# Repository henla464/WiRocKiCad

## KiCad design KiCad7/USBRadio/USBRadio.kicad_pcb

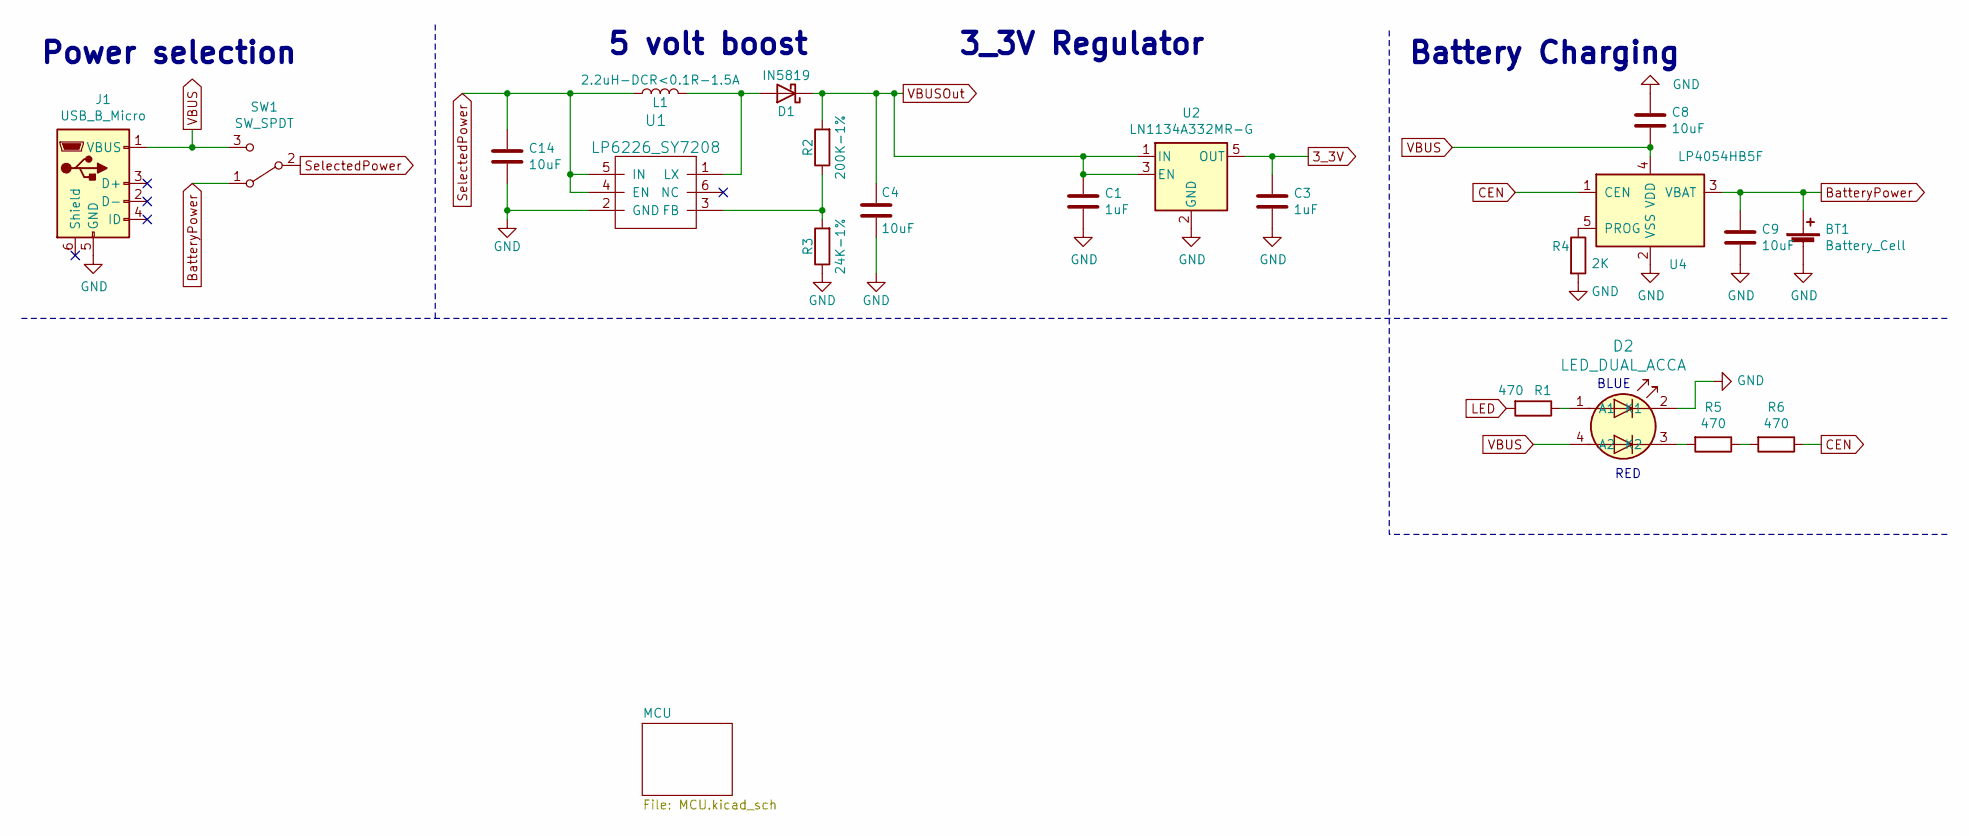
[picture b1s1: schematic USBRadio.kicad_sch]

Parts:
BT1: Battery_Cell; JST_2.56
C1, C3: 1uF; C_0603_1608Metric_Pad1.08x0.95mm_HandSolder; ManufacturerPartNumber CL10A105KB8NNNC; LCSC Part # C15849
C4, C8, C9, C14: 10uF; C_0603_1608Metric_Pad1.08x0.95mm_HandSolder; ManufacturerPartNumber CL10A106KP8NNNC; LCSC Part # C19702
D1: IN5819; D_SOD-123; ManufacturerPartNumber B5817W; LCSC Part # C8597
D2: LED_DUAL_ACCA; LED_Dual_1.7_1.6; ManufacturerPartNumber HL-PCB-1617S9FH203BC; LCSC Part # C513363
J1: USB_B_Micro; USB_Micro-B_Horizontal; ManufacturerPartNumber U254-051T-4BH83-F1S; LCSC Part # C397452
L1: 2.2uH-DCR<0.1R-1.5A; Inductor_SLW4018; ManufacturerPartNumber SLW4018S2R2MST; LCSC Part # C206341
R1, R5, R6: 470; R_0805_2012Metric_Pad1.20x1.40mm_HandSolder; ManufacturerPartNumber 0805W8F4700T5E; LCSC Part # C17710
R2: 200K-1%; C_0603_1608Metric_Pad1.08x0.95mm_HandSolder; ManufacturerPartNumber 0603WAF2003T5E; LCSC Part # C25811
R3: 24K-1%; C_0603_1608Metric_Pad1.08x0.95mm_HandSolder; ManufacturerPartNumber 0603WAF2402T5E; LCSC Part # C23352
R4: 2K; R_0805_2012Metric_Pad1.20x1.40mm_HandSolder; ManufacturerPartNumber 0805W8F2001T5E; LCSC Part # C17604
SW1: SW_SPDT; SW_SPDT_PCM12; ManufacturerPartNumber SK-3296S-01-L3; LCSC Part # C319019
U1: LP6226_SY7208; TSOT-23-6_HandSoldering; ManufacturerPartNumber SY7208ABC; LCSC Part # C80514
U2: LN1134A332MR-G; SOT-23-5; ManufacturerPartNumber LN1134A332MR-G; LCSC Part # C141419
U4: LP4054HB5F; SOT-23-5; ManufacturerPartNumber LP4054HB5F; LCSC Part # C517187

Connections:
3_3V: C3.1, U2.5 (OUT); also elsewhere on the board
BatteryPower: BT1.1 (+), C9.1, SW1.1 (A), U4.3 (VBAT)
CEN: R6.1, U4.1 (CEN)
GND: BT1.2 (-), C1.2, C3.2, C4.2, C8.1, C9.2, C14.2, D2.2 (K1), J1.5 (GND), R3.1, R4.2, U1.2 (GND), U2.2 (GND), U4.2 (VSS); also elsewhere on the board
LED: R1.2; also elsewhere on the board
unnamed: D1.2 (A), L1.2, U1.1 (LX)
unnamed: D2.1 (A1), R1.1
unnamed: D2.3 (K2), R5.2
unnamed: R5.1, R6.2
unnamed: R2.1, R3.2, U1.3 (FB)
unnamed: R4.1, U4.5 (PROG)
SelectedPower: C14.1, L1.1, SW1.2 (B), U1.4 (EN), U1.5 (IN)
VBUS: C8.2, D2.4 (A2), J1.1 (VBUS), SW1.3 (C), U4.4 (VDD)
VBUSOut: C1.1, C4.1, D1.1 (K), R2.2, U2.1 (IN), U2.3 (EN); also elsewhere on the board

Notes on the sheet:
RED
Power selection
BLUE
5 volt boost
3_3V Regulator
Battery Charging

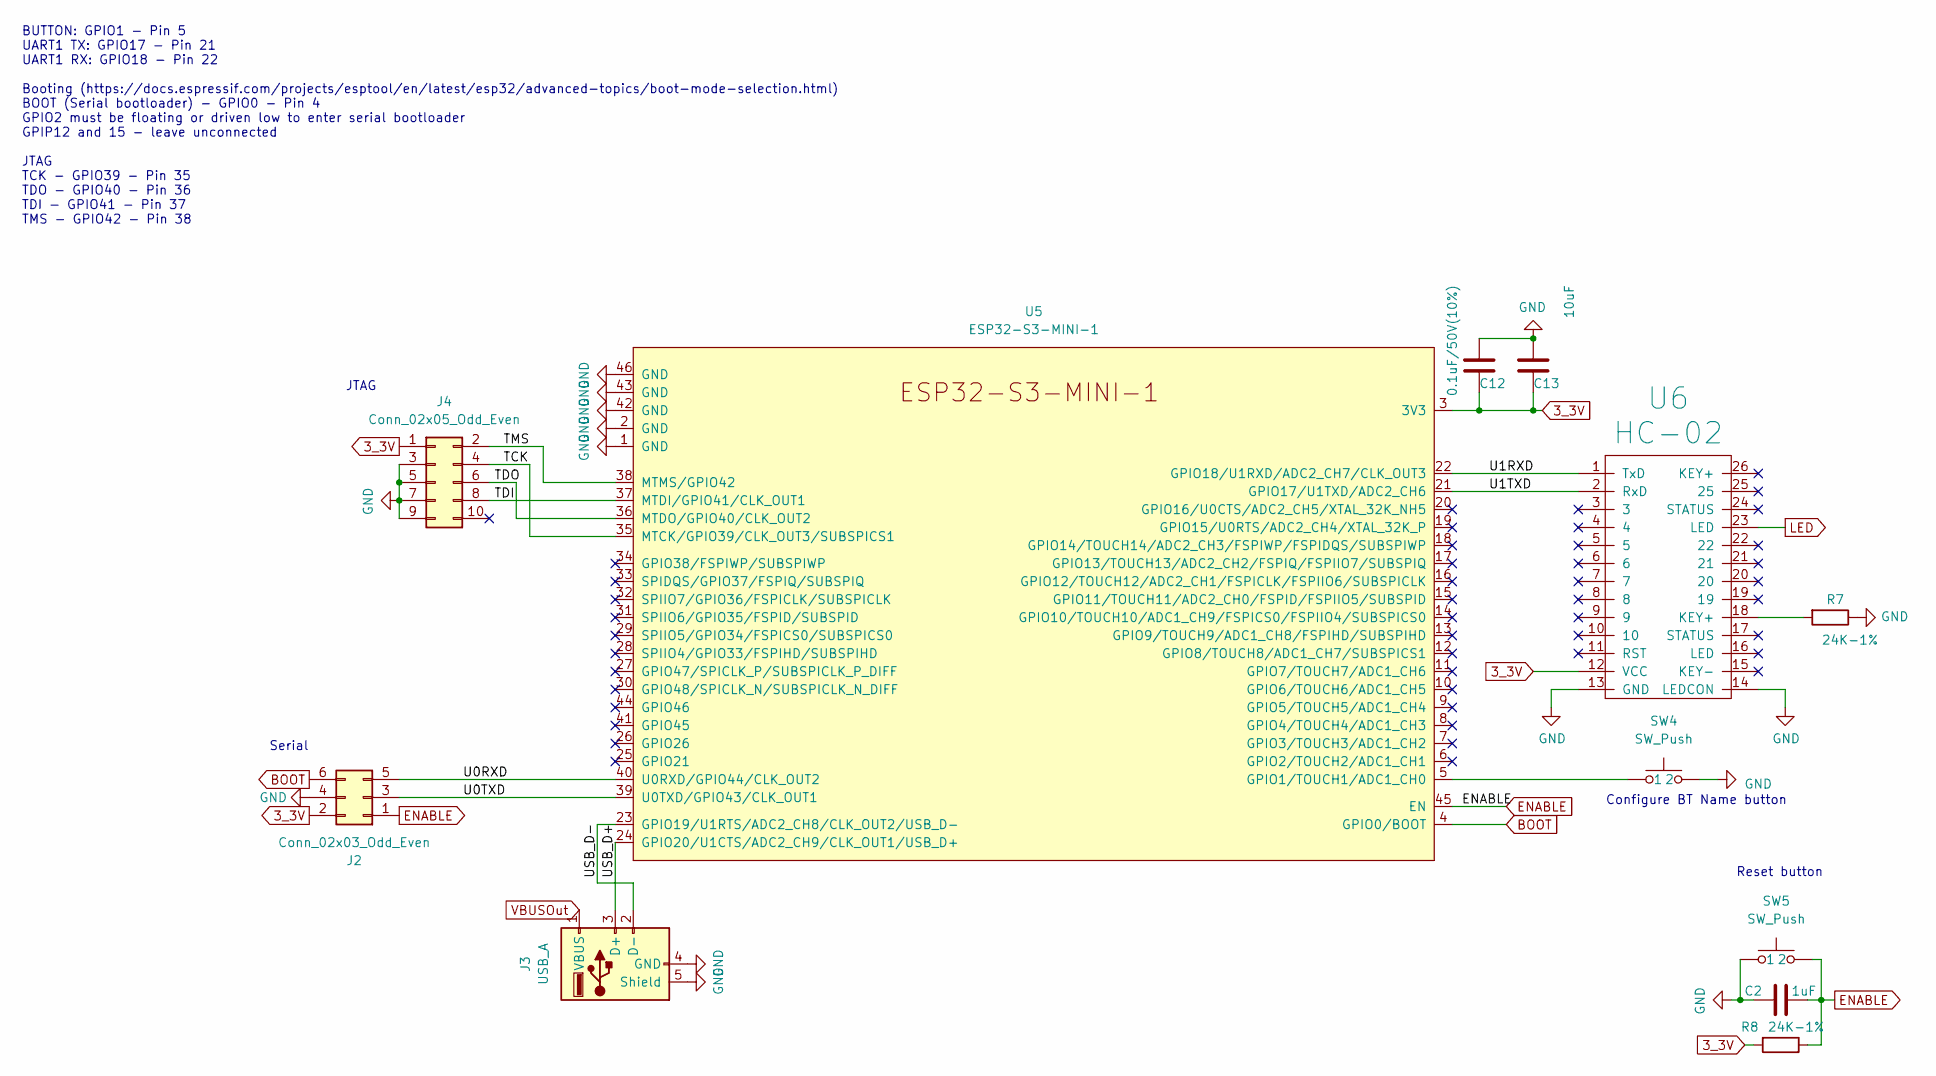
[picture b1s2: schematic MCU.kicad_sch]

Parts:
C2: 1uF; C_0603_1608Metric_Pad1.08x0.95mm_HandSolder; ManufacturerPartNumber CL10A105KB8NNNC; LCSC Part # C15849
C12: 0.1uF/50V(10%); C_0805_2012Metric_Pad1.18x1.45mm_HandSolder; ManufacturerPartNumber CC0805KRX7R9BB104; LCSC Part # C49678
C13: 10uF; C_0603_1608Metric_Pad1.08x0.95mm_HandSolder; ManufacturerPartNumber CL10A106KP8NNNC; LCSC Part # C19702
J2: Conn_02x03_Odd_Even; IDC-Header_2x03_P1.27mm_Vertical_SMD
J3: USB_A; USB_A_CONNFLY_DS1095-WNR0
J4: Conn_02x05_Odd_Even; IDC-Header_2x05_P1.27mm_Vertical_SMD
R7, R8: 24K-1%; C_0603_1608Metric_Pad1.08x0.95mm_HandSolder; ManufacturerPartNumber 0603WAF2402T5E; LCSC Part # C23352
SW4, SW5: SW_Push; SW_SPST_TL3342; ManufacturerPartNumber TS-1187A-B-A-B; LCSC Part # C318884
U5: ESP32-S3-MINI-1
U6: HC-02

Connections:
3_3V: C12.1, C13.1, J2.2, J4.1, R8.2, U5.3 (3V3), U6.12 (VCC); also elsewhere on the board
/MCU/TCK: J4.4, U5.35 (MTCK/GPIO39/CLK_OUT3/SUBSPICS1)
/MCU/TDI: J4.8, U5.37 (MTDI/GPIO41/CLK_OUT1)
/MCU/TDO: J4.6, U5.36 (MTDO/GPIO40/CLK_OUT2)
/MCU/TMS: J4.2, U5.38 (MTMS/GPIO42)
/MCU/U0RXD: J2.5, U5.40 (U0RXD/GPIO44/CLK_OUT2)
/MCU/U0TXD: J2.3, U5.39 (U0TXD/GPIO43/CLK_OUT1)
/MCU/U1RXD: U5.22 (GPIO18/U1RXD/ADC2_CH7/CLK_OUT3), U6.1 (TxD)
/MCU/U1TXD: U5.21 (GPIO17/U1TXD/ADC2_CH6), U6.2 (RxD)
/MCU/USB_D+: J3.3 (D+), U5.24 (GPIO20/U1CTS/ADC2_CH9/CLK_OUT1/USB_D+)
/MCU/USB_D-: J3.2 (D-), U5.23 (GPIO19/U1RTS/ADC2_CH8/CLK_OUT2/USB_D-)
BOOT: J2.6, U5.4 (GPIO0/BOOT)
ENABLE: C2.2, J2.1, R8.1, SW5.2, U5.45 (EN)
GND: C2.1, C12.2, C13.2, J2.4, J3.4 (GND), J3.5 (Shield), J4.3, J4.5, J4.7, J4.9, R7.1, SW4.2, SW5.1, U5.1 (GND), U5.2 (GND), U5.42 (GND), U5.43 (GND), U5.46 (GND), U6.13 (GND), U6.14 (LEDCON); also elsewhere on the board
LED: U6.23 (LED); also elsewhere on the board
unnamed: R7.2, U6.18 (KEY+)
unnamed: SW4.1, U5.5 (GPIO1/TOUCH1/ADC1_CH0)
VBUSOut: J3.1 (VBUS); also elsewhere on the board

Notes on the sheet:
Reset button
JTAG
BUTTON: GPIO1 - Pin 5 UART1 TX: GPIO17 - Pin 21 UART1 RX: GPIO18 - Pin 22 Booting (https://docs.espressif.com/projects/esptool/en/latest/esp32/advanced-topics/boot-mode-selection.html) BOOT (Serial bootloader) - GPIO0 - Pin 4 GPIO2 must be floating or driven low to enter serial bootloader GPIP12 an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
Serial
Configure BT Name button

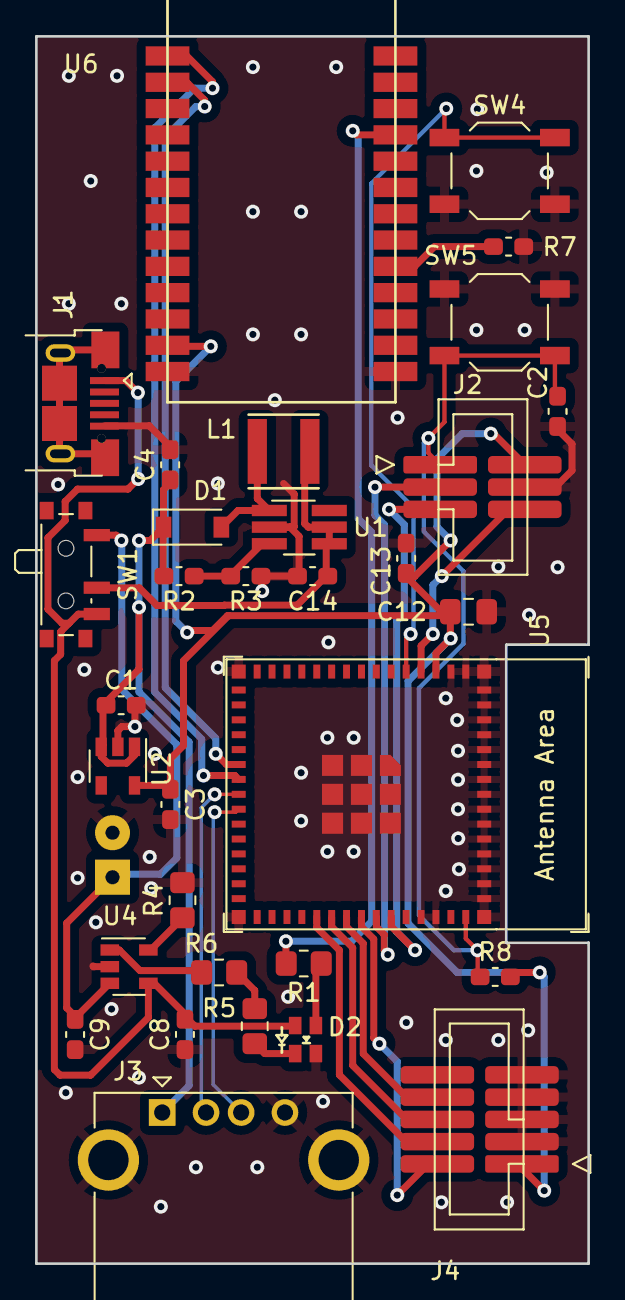
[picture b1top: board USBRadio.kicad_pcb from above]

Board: 2 copper layers, 31.5 x 70.0 mm, 33 parts (1 on the bottom side), 28 nets.

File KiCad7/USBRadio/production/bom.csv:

Designator,Footprint,Quantity,Value,LCSC Part #
BT1,JST_2.56,1,Battery_Cell,
"C1, C2, C3",C_0603_1608Metric_Pad1.08x0.95mm_HandSolder,3,1uF,
C12,C_0805_2012Metric_Pad1.18x1.45mm_HandSolder,1,0.1uF/50V(10%),
"C13, C14, C4, C8, C9",C_0603_1608Metric_Pad1.08x0.95mm_HandSolder,5,10uF,
D1,D_SOD-123,1,IN5819,
D2,LED_Dual_1.7_1.6,1,LED_DUAL_ACCA,
J1,USB_Micro-B_Horizontal,1,USB_B_Micro,
J2,IDC-Header_2x03_P1.27mm_Vertical_SMD,1,Conn_02x03_Odd_Even,
J3,USB_A_CONNFLY_DS1095-WNR0,1,USB_A,
J4,IDC-Header_2x05_P1.27mm_Vertical_SMD,1,Conn_02x05_Odd_Even,
L1,Inductor_SLW4018,1,2.2uH-DCR<0.1R-1.5A,
"R1, R5, R6",R_0805_2012Metric_Pad1.20x1.40mm_HandSolder,3,470,
R2,C_0603_1608Metric_Pad1.08x0.95mm_HandSolder,1,200K-1%,
"R3, R7, R8",C_0603_1608Metric_Pad1.08x0.95mm_HandSolder,3,24K-1%,
R4,R_0805_2012Metric_Pad1.20x1.40mm_HandSolder,1,2K,
SW1,SW_SPDT_PCM12,1,SW_SPDT,
"SW4, SW5",SW_SPST_TL3342,2,SW_Push,
U1,TSOT-23-6_HandSoldering,1,LP6226_SY7208,
U2,SOT-23-5,1,LN1134A332MR-G,
U4,SOT-23-5,1,LP4054HB5F,
U5,ESP32-S3-MINI-1,1,ESP32-S3-MINI-1,
U6,HC-02,1,HC-02,

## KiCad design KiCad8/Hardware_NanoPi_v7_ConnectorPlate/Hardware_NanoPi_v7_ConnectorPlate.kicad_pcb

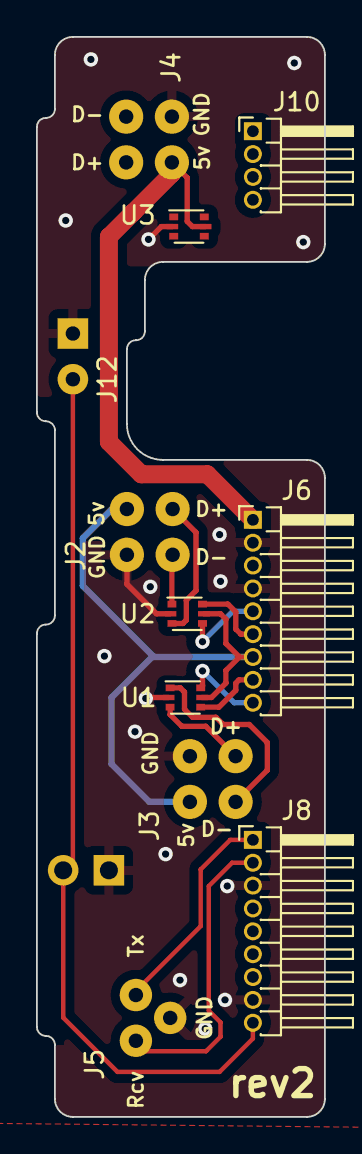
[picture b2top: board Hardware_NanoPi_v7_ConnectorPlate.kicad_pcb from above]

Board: 2 copper layers, 16.0 x 60.0 mm, 12 parts (1 on the bottom side), 14 nets.

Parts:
J2: USB_Host_Data_02x02; USBConnPads7
J3: USB_Host_Data_02x02; USBConnPads8
J4: USB_Power_02x02; USBConnPads7
J5: Conn_01x03; SerialConnPads3Pin
J6, J8: Conn_01x09; PinHeader_1x09_P1.27mm_Horizontal
J10: Conn_01x04; PinHeader_1x04_P1.27mm_Horizontal
J11: Conn_01x02; PinHeader_1x02_P2.54mm_Horizontal
J12: Conn_01x02; PwrBtnPads
U1, U2, U3: USBLC6-2P6; SOT-666

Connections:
GND: J2.4, J3.4, J4.4, J5.3, J6.2, J6.4, J8.3, J8.8, J11.1, J12.1, U1.2 (GND), U2.2 (GND), U3.2 (GND)
unnamed: J2.2, U2.1 (I/O1)
unnamed: J2.3, U2.3 (I/O2)
unnamed: J3.2, U1.1 (I/O1)
unnamed: J3.3, U1.3 (I/O2)
PWRBTN: J8.9, J11.2, J12.2
R2IN: J5.1, J8.2
T2OUT: J5.2, J8.1
USBHost-DM1: J6.6, U2.6 (I/O1)
USBHost-DM2: J6.9, U1.6 (I/O1)
USBHost-DP1: J6.5, U2.4 (I/O2)
USBHost-DP2: J6.8, U1.4 (I/O2)
VBUS: J4.1, J6.1, U3.5 (VBUS)
VDD_5V: J2.1, J3.1, J6.7, U1.5 (VBUS), U2.5 (VBUS)

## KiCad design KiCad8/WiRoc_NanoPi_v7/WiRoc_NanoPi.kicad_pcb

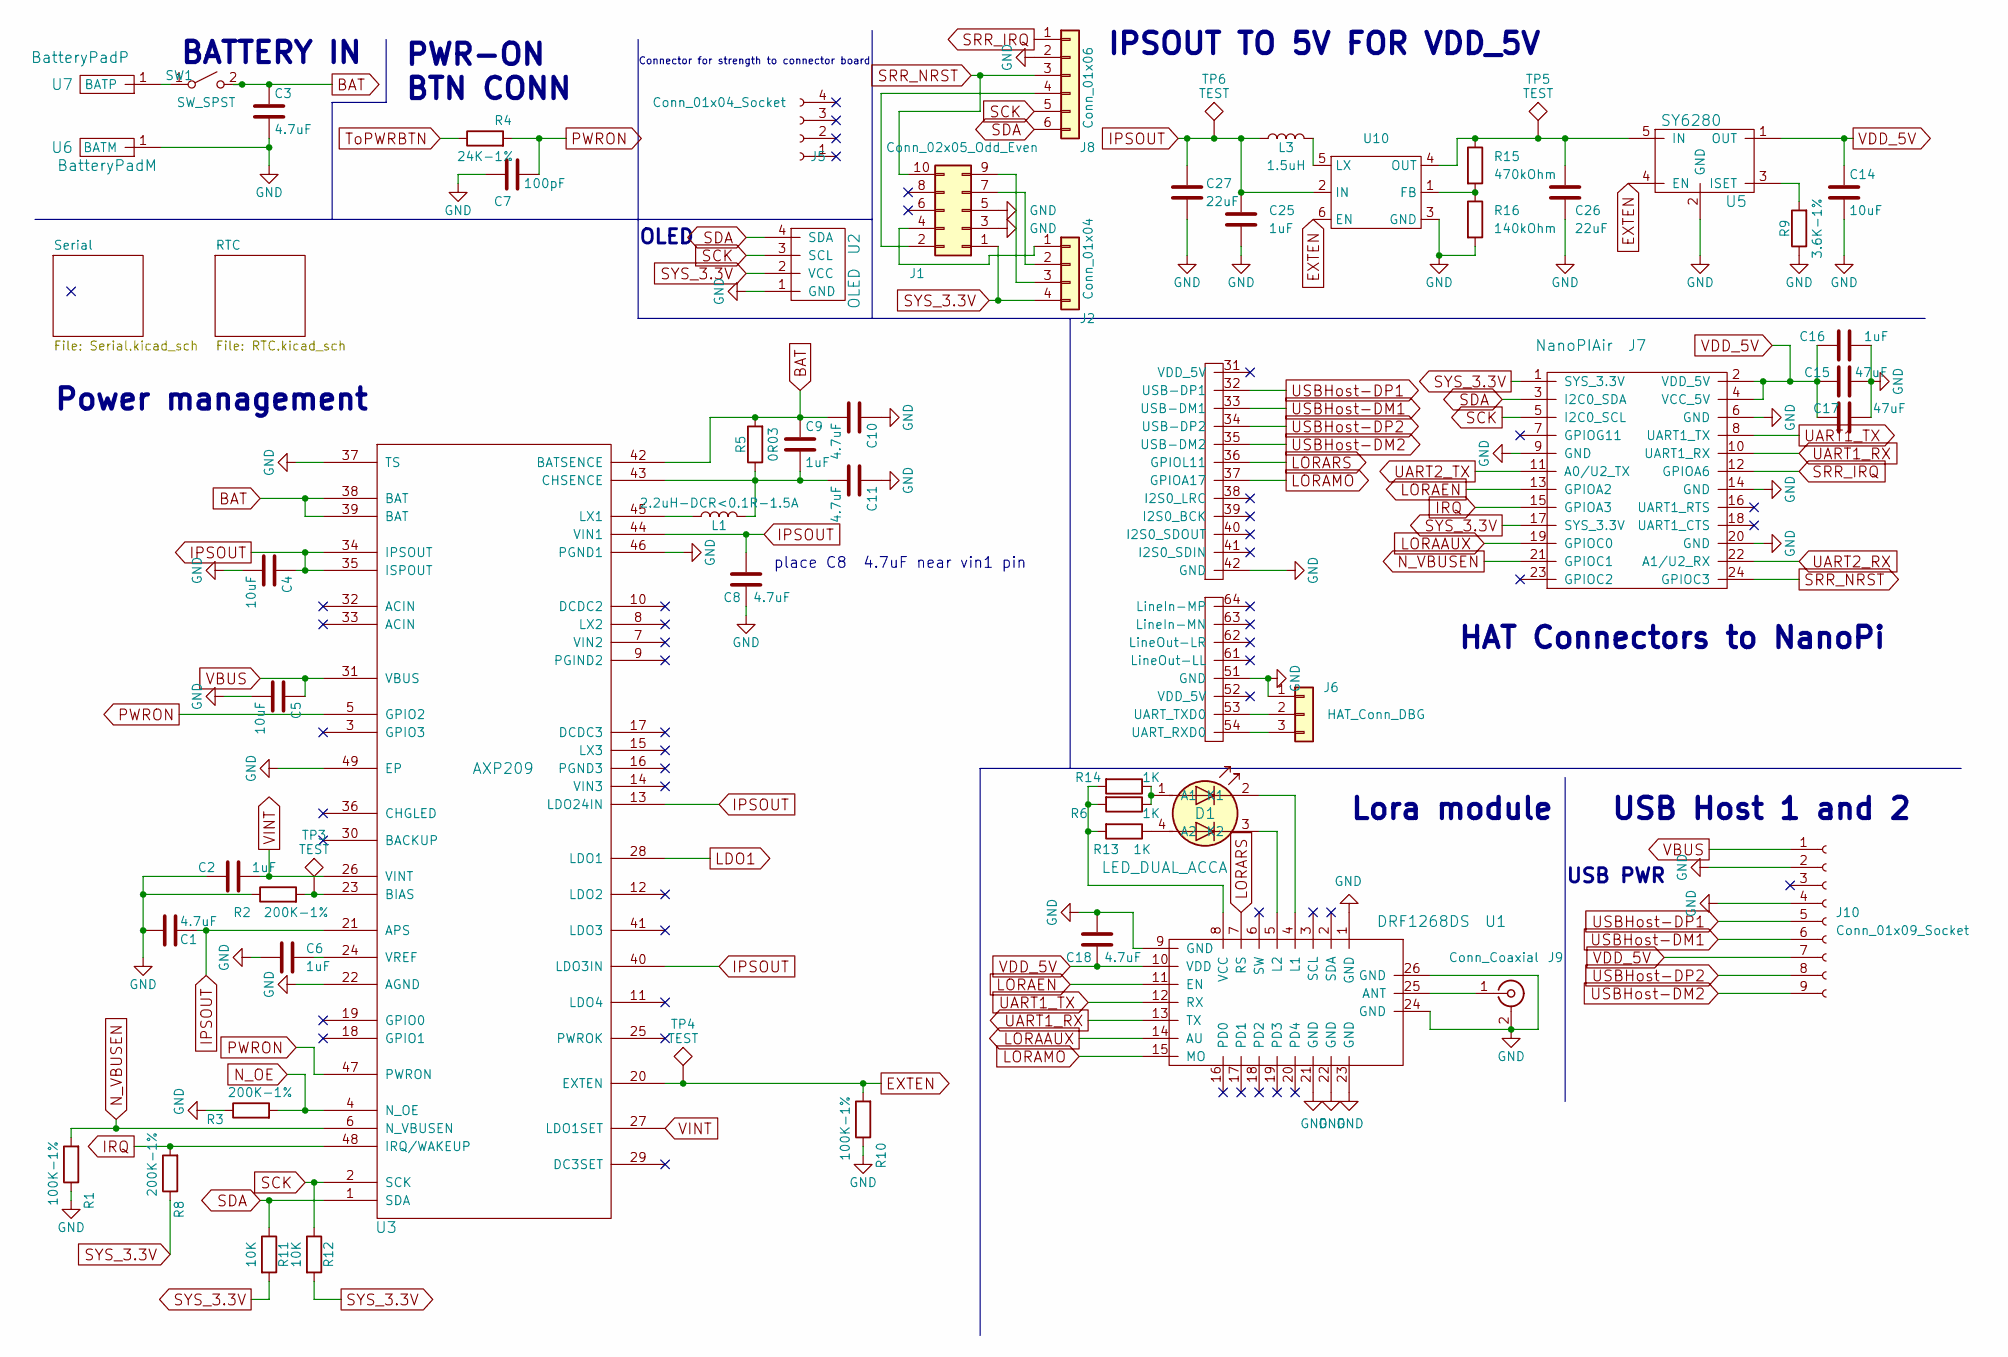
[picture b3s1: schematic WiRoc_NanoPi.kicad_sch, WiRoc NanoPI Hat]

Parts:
C1, C3, C8, C10, C11, C18: 4.7uF; C_0603_1608Metric; ManufacturerPartNumber CL10A475KO8NNNC; LCSC Part # C19666
C2, C6, C9, C16, C25: 1uF; C_0603_1608Metric; ManufacturerPartNumber CL10A105KB8NNNC; LCSC Part # C15849
C4, C5, C14: 10uF; C_0603_1608Metric; ManufacturerPartNumber CL10A106KP8NNNC; LCSC Part # C19702
C7: 100pF; C_0603_1608Metric; ManufacturerPartNumber CL10C101JB8NNNC; LCSC Part # C14858
C15, C17: 47uF; C_1206_3216Metric; ManufacturerPartNumber CL31A476MPHNNNE; LCSC Part # C96123
C26, C27: 22uF; C_0603_1608Metric; PartNo GRM188R61A226ME15D; LCSC Part # C84419
D1: LED_DUAL_ACCA; LED_Dual_1.7_1.6; ManufacturerPartNumber HL-PCB-1617S9FH203BC; LCSC Part # C513363
J1: Conn_02x05_Odd_Even; PinHeader_2x05_P1.27mm_Vertical
J2: Conn_01x04; PinHeader_1x04_P1.27mm_Horizontal
J5: Conn_01x04_Socket; PinSocket_1x04_P1.27mm_Vertical
J6: HAT_Conn_DBG; Pin_Header_Straight_1x03_Pitch2.54mm; ManufacturerPartNumber 2.54mm 1x40P
J7: NanoPIAir; NanoPiNeoAirAllPins; ManufacturerPartNumber 2.54mm 2x40P
J8: Conn_01x06; PinHeader_1x06_P1.27mm_Horizontal
J9: Conn_Coaxial; SMA_Amphenol_901-143_Horizontal
J10: Conn_01x09_Socket; PinSocket_1x09_P1.27mm_Vertical
L1: 2.2uH-DCR<0.1R-1.5A; Inductor_SLW4018; ManufacturerPartNumber SLW4018S2R2MST; LCSC Part # C206341
L3: 1.5uH; Inductor_SLW4018; PartNo SLW4020S1R5MST; LCSC Part # C206395
R1, R10: 100K-1%; R_0603_1608Metric; ManufacturerPartNumber 0603WAF1003T5E; LCSC Part # C25803
R2, R3, R8: 200K-1%; R_0603_1608Metric; ManufacturerPartNumber 0603WAF2003T5E; LCSC Part # C25811
R4: 24K-1%; R_0603_1608Metric; ManufacturerPartNumber 0603WAF2402T5E; LCSC Part # C23352
R5: 0R03; R_0805_2012Metric; ManufacturerPartNumber 0805W4F300MT5E; LCSC Part # C247605
R6, R13, R14: 1K; R_0603_1608Metric; ManufacturerPartNumber 0603WAJ0102T5E; LCSC Part # C21190
R9: 3.6K-1%; R_0603_1608Metric; ManufacturerPartNumber 0603WAF3601T5E; LCSC Part # C22980
R11, R12: 10K; R_0603_1608Metric; ManufacturerPartNumber 0603WAF1002T5E; LCSC Part # C25804
R15: 470kOhm; R_0603_1608Metric; PartNo HPCR0603F470KK9; LCSC Part # C23178
R16: 140kOhm; R_0603_1608Metric; PartNo 0603WAF140KT5E; LCSC Part # C321721
SW1: SW_SPST; Pin_Header_Straight_1x02_Pitch2.54mm; ManufacturerPartNumber 2.54mm 1x40P
TP3, TP4, TP5, TP6: TEST; TestPoint_Pad_D1.0mm
U1: DRF1268DS
U2: OLED; CONN_OLED_TWI-Socket_Strip_Straight_1x04_Pitch2.54mm; ManufacturerPartNumber 2.54mm 1x40P
U3: AXP209; qfn48_6x6mm_Pitch0.4mm; ManufacturerPartNumber AXP209; LCSC Part # C2997895
U5: SY6280; SOT-23-5; ManufacturerPartNumber SY6280AAC; LCSC Part # C55136
U6: BatteryPadM; BatteryPad
U7: BatteryPadP; BatteryPad
U10: TSOT-23-6; PartNo SY7069ADC; LCSC Part # C207630

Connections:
BAT: C3.1, C9.1, C10.2, R5.2, SW1.2 (B), U3.38 (BAT), U3.39 (BAT), U3.42 (BATSENCE)
EXTEN: R10.2, TP4.1, U3.20 (EXTEN), U5.4 (EN), U10.6 (EN)
GND: C1.2, C2.2, C3.2, C4.2, C5.2, C6.2, C7.1, C8.1, C10.1, C11.1, C14.2, C15.1, C16.2, C17.1, C18.2, C25.2, C26.2, C27.2, J1.3, J1.5, J6.1, J7.6 (GND), J7.9 (GND), J7.14 (GND), J7.20 (GND), J7.42 (GND), J7.51 (GND), J8.2, J9.2 (Ext), J10.2, J10.4, R1.1, R2.1, R3.1, R9.1, R10.1, R16.2, U1.1 (GND), U1.9 (GND), U1.21 (GND), U1.22 (GND), U1.23 (GND), U1.24 (GND), U1.26 (GND), U2.1 (GND), U3.22 (AGND), U3.37 (TS), U3.46 (PGND1), U3.49 (EP), U5.2 (GND), U6.1 (BATM), U10.3 (GND); also elsewhere on the board
IPSOUT: C1.1, C4.1, C8.2, C25.1, C27.1, L3.1, TP6.1, U3.13 (LDO24IN), U3.21 (APS), U3.34 (IPSOUT), U3.35 (ISPOUT), U3.40 (LDO3IN), U3.44 (VIN1), U10.2 (IN)
IRQ: J7.15 (GPIOA3), R8.2, U3.48 (IRQ/WAKEUP)
LDO1: U3.28 (LDO1); also elsewhere on the board
LORAAUX: J7.19 (GPIOC0), U1.14 (AU)
LORAEN: J7.13 (GPIOA2), U1.11 (EN)
LORAMO: J7.37 (GPIOA17), U1.15 (MO)
LORARS: J7.36 (GPIOL11), U1.7 (RS)
N_OE: R3.2, U3.4 (N_OE); also elsewhere on the board
N_VBUSEN: J7.21 (GPIOC1), R1.2, U3.6 (N_VBUSEN)
unnamed: D1.1 (A1), R6.1, R14.1
unnamed: D1.4 (A2), R13.1
unnamed: D1.2 (K1), U1.4 (L1)
unnamed: D1.3 (K2), U1.5 (L2)
unnamed: J1.2, J8.4
unnamed: J1.4, J2.1
unnamed: J1.7, J2.2
unnamed: J1.9, J2.3
unnamed: J6.2, J7.53 (UART_TXD0)
unnamed: J6.3, J7.54 (UART_RXD0)
unnamed: J9.1 (In), U1.25 (ANT)
unnamed: SW1.1 (A), U7.1 (BATP)
unnamed: R6.2, R13.2, R14.2, U1.8 (VCC)
unnamed: R2.2, TP3.1, U3.23 (BIAS)
unnamed: C9.2, C11.2, L1.2, R5.1, U3.43 (CHSENCE)
unnamed: L1.1, U3.45 (LX1)
unnamed: C6.1, U3.24 (VREF)
unnamed: R9.2, U5.3 (ISET)
unnamed: R15.2, R16.1, U10.1 (FB)
unnamed: L3.2, U10.5 (LX)
unnamed: C26.1, R15.1, TP5.1, U5.5 (IN), U10.4 (OUT)
PWRON: C7.2, R4.2, U3.5 (GPIO2), U3.47 (PWRON)
SCK: J7.5 (I2C0_SCL), J8.5, R12.1, U2.3 (SCL), U3.2 (SCK); also elsewhere on the board
SDA: J7.3 (I2C0_SDA), J8.6, R11.1, U2.4 (SDA), U3.1 (SDA); also elsewhere on the board
SRR_IRQ: J7.12 (GPIOA6), J8.1
SRR_NRST: J1.10, J7.24 (GPIOC3), J8.3
SYS_3.3V: J1.1, J2.4, J7.1 (SYS_3.3V), J7.17 (SYS_3.3V), R8.1, R11.2, R12.2, U2.2 (VCC); also elsewhere on the board
ToPWRBTN: R4.1; also elsewhere on the board
UART1_RX: J7.10 (UART1_RX), U1.13 (TX)
UART1_TX: J7.8 (UART1_TX), U1.12 (RX)
UART2_RX: J7.22 (A1/U2_RX); also elsewhere on the board
UART2_TX: J7.11 (A0/U2_TX); also elsewhere on the board
USBHost-DM1: J7.33 (USB-DM1), J10.6
USBHost-DM2: J7.35 (USB-DM2), J10.9
USBHost-DP1: J7.32 (USB-DP1), J10.5
USBHost-DP2: J7.34 (USB-DP2), J10.8
VBUS: C5.1, J10.1, U3.31 (VBUS)
VDD_5V: C14.1, C15.2, C16.1, C17.2, C18.1, J7.2 (VDD_5V), J7.4 (VCC_5V), J10.7, U1.10 (VDD), U5.1 (OUT)
VINT: C2.1, U3.26 (VINT), U3.27 (LDO1SET)

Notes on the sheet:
place C8 4.7uF near vin1 pin
USB PWR
Lora module
HAT Connectors to NanoPi
IPSOUT TO 5V FOR VDD_5V
PWR-ON BTN CONN
Power management
OLED
Connector for strength to connector board
USB Host 1 and 2
BATTERY IN

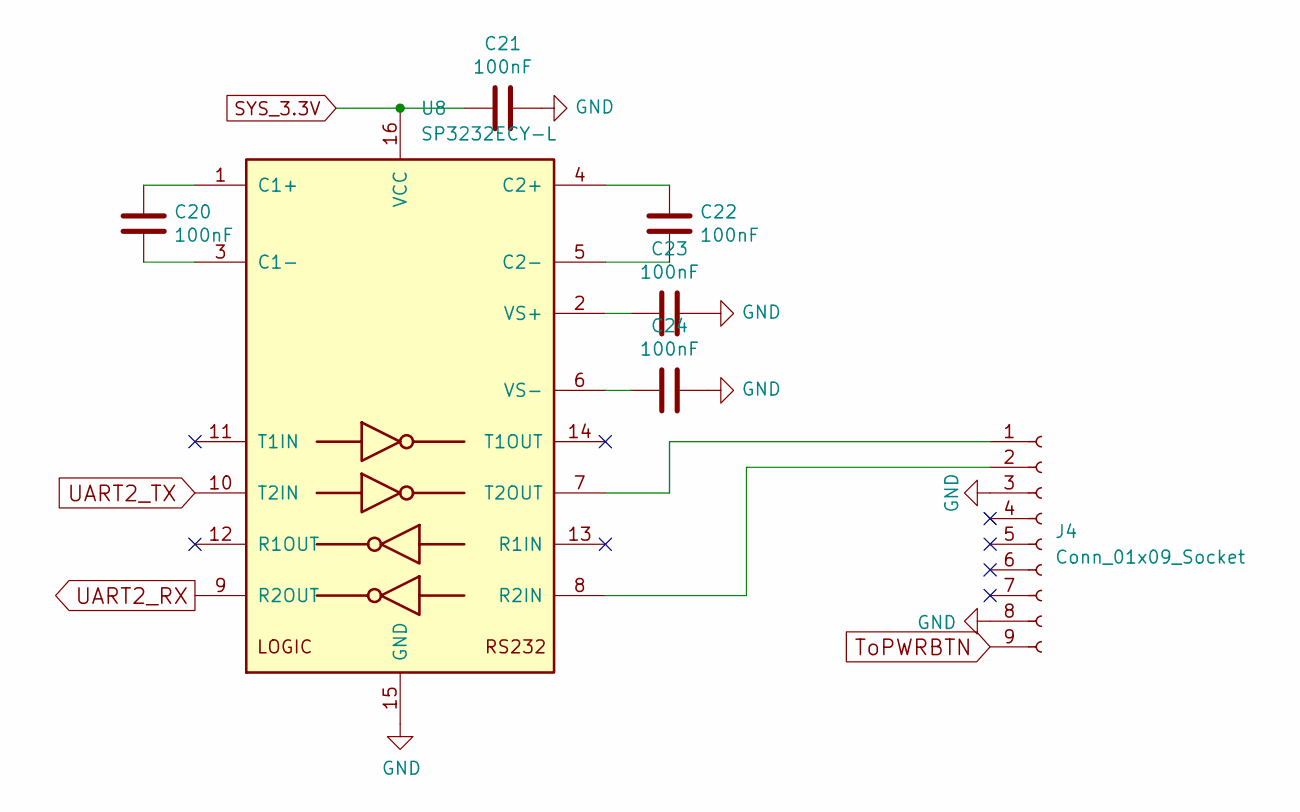
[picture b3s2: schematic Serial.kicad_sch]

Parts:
C20, C21, C22, C23, C24: 100nF; C_0603_1608Metric; ManufacturerPartNumber CC0603KRX7R9BB104; LCSC Part # C14663
J4: Conn_01x09_Socket; PinSocket_1x09_P1.27mm_Vertical
U8: SP3232ECY-L; TSSOP-16_4.4x5mm_P0.65mm; ManufacturerPartNumber SP3232ECY-L; LCSC Part # C3028967

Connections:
GND: C21.1, C23.1, C24.1, J4.3, J4.8, U8.15 (GND); also elsewhere on the board
unnamed: J4.1, U8.7 (T2OUT)
unnamed: J4.2, U8.8 (R2IN)
unnamed: C20.1, U8.1 (C1+)
unnamed: C20.2, U8.3 (C1-)
unnamed: C22.1, U8.4 (C2+)
unnamed: C22.2, U8.5 (C2-)
unnamed: C23.2, U8.2 (VS+)
unnamed: C24.2, U8.6 (VS-)
SYS_3.3V: C21.2, U8.16 (VCC); also elsewhere on the board
ToPWRBTN: J4.9; also elsewhere on the board
UART2_RX: U8.9 (R2OUT); also elsewhere on the board
UART2_TX: U8.10 (T2IN); also elsewhere on the board

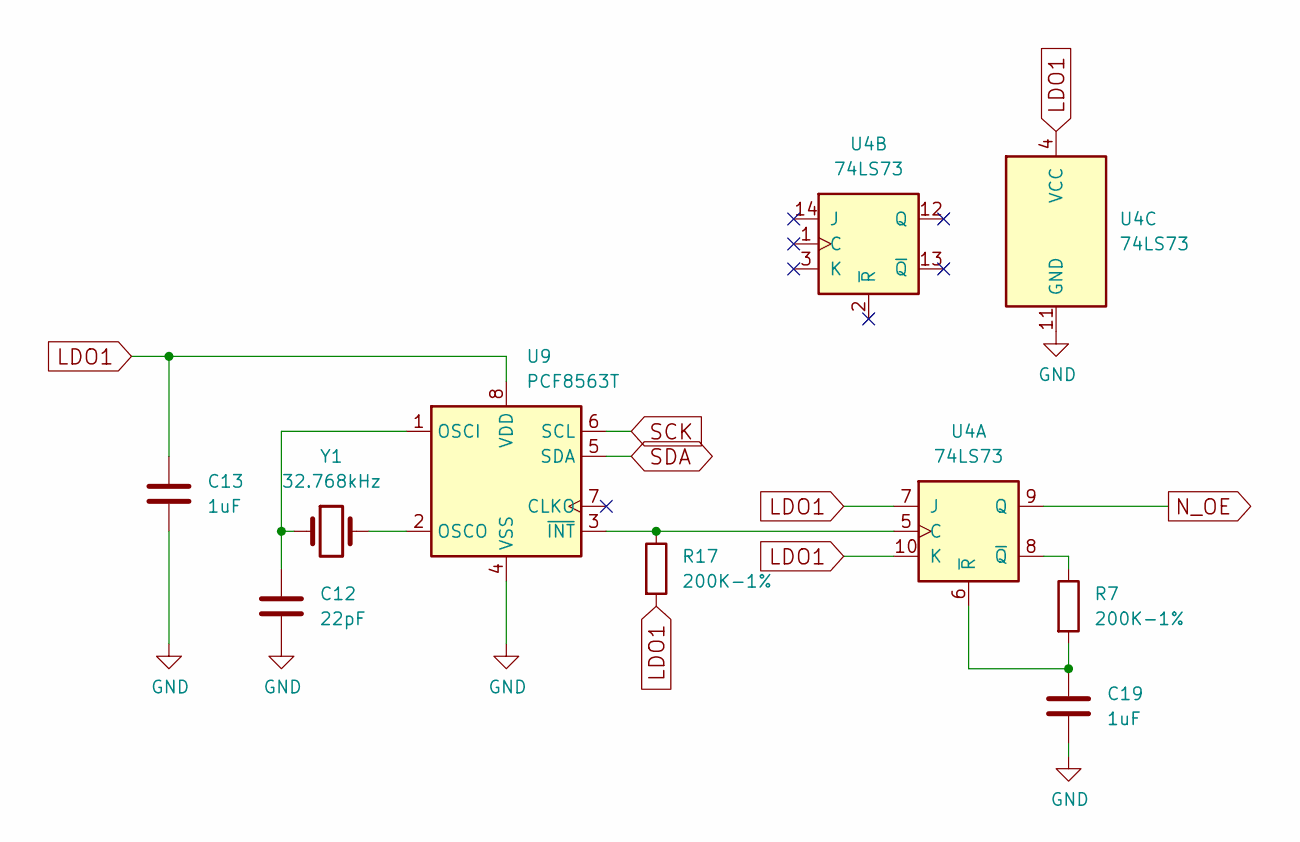
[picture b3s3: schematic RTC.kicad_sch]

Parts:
C12: 22pF; C_0402_1005Metric; ManufacturerPartNumber GRM155R71C223JA01D; LCSC Part # C1555
C13, C19: 1uF; C_0603_1608Metric; ManufacturerPartNumber CL10A105KB8NNNC; LCSC Part # C15849
R7, R17: 200K-1%; R_0603_1608Metric; ManufacturerPartNumber 0603WAF2003T5E; LCSC Part # C25811
U4: 74LS73; SOIC-14_3.9x8.7mm_P1.27mm; ManufacturerPartNumber CD74HC73M96; LCSC Part # C350539
U9: PCF8563T; SOIC-8_3.9x4.9mm_P1.27mm; ManufacturerPartNumber PCF8563T/5,518; LCSC Part # C7440
Y1: 32.768kHz; SMD3215-2P; ManufacturerPartNumber Q13FC1350000400; LCSC Part # C32346

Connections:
GND: C12.2, C13.2, C19.2, U4.11 (GND), U9.4 (VSS); also elsewhere on the board
LDO1: C13.1, R17.2, U4.4 (VCC), U4.7 (J), U4.10 (K), U9.8 (VDD); also elsewhere on the board
N_OE: U4.9 (Q); also elsewhere on the board
unnamed: R17.1, U4.5 (C), U9.3 (~INT)
unnamed: R7.1, U4.8 (~Q)
unnamed: C19.1, R7.2, U4.6 (~R)
unnamed: C12.1, U9.1 (OSCI), Y1.1
unnamed: U9.2 (OSCO), Y1.2
SCK: U9.6 (SCL); also elsewhere on the board
SDA: U9.5 (SDA); also elsewhere on the board

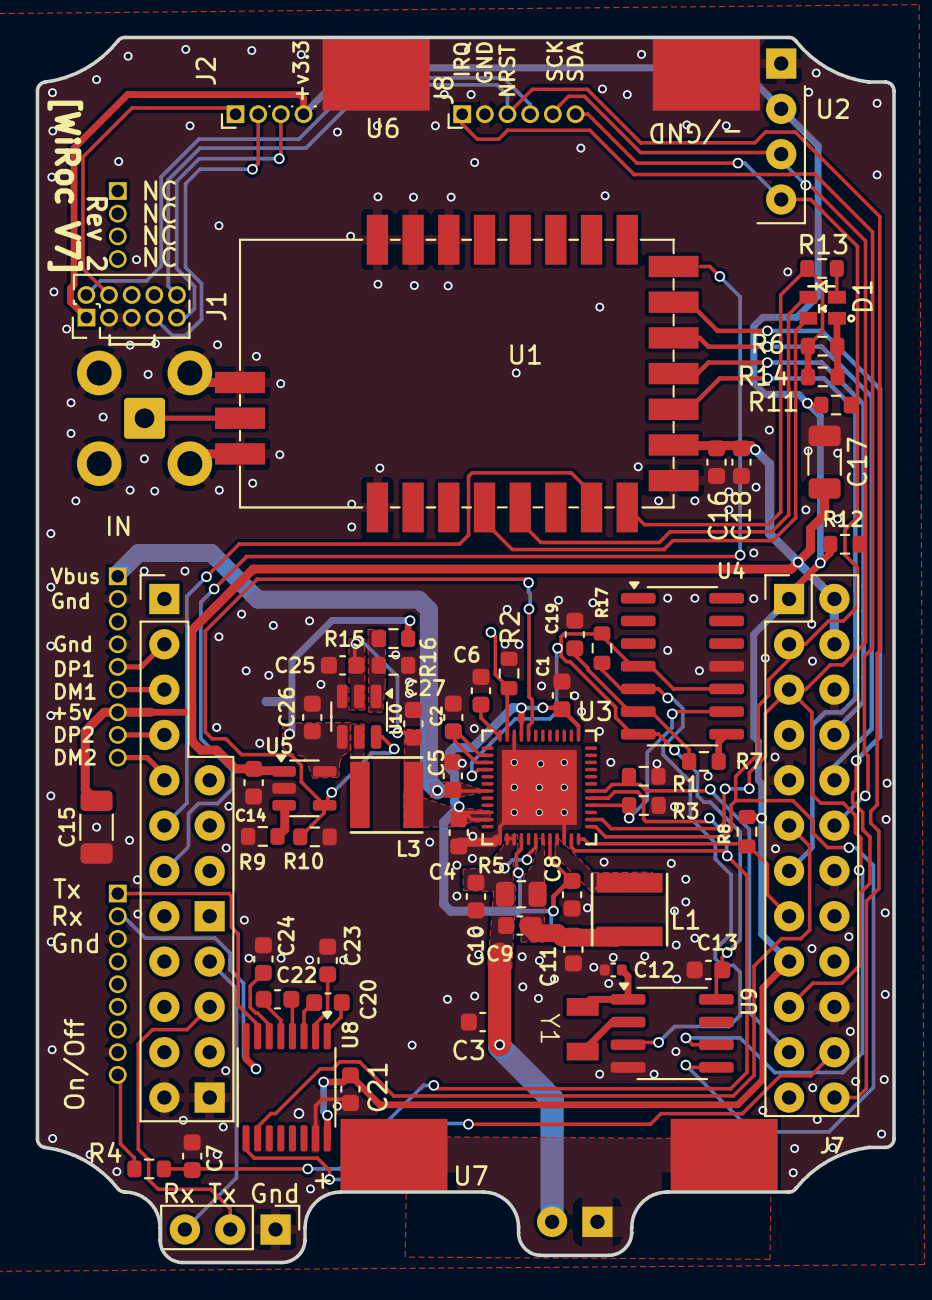
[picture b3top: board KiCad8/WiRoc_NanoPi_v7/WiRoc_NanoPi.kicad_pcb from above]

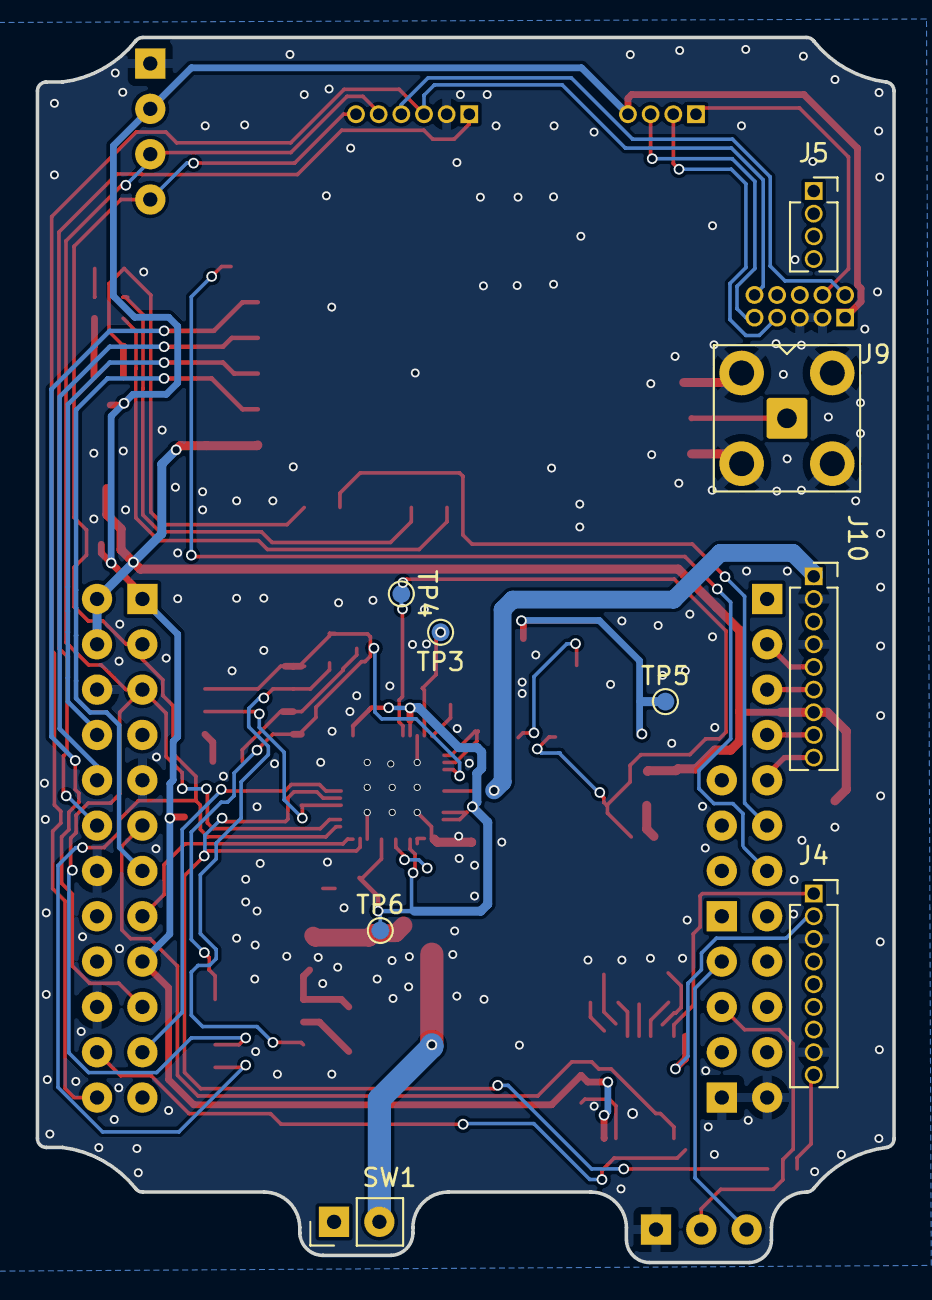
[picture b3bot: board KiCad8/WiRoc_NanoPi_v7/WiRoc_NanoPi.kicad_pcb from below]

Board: 4 copper layers, 48.0 x 68.7 mm, 72 parts (9 on the bottom side), 64 nets.

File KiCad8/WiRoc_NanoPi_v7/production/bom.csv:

Designator,Footprint,Quantity,Value,LCSC Part #
"C1, C10, C11, C18, C3, C8",0603,6,4.7uF,C19666
C12,0402,1,22pF,C1555
"C13, C16, C19, C2, C25, C6, C9",0603,7,1uF,C15849
"C14, C4, C5",0603,3,10uF,C19702
"C15, C17",1206,2,47uF,C96123
"C20, C21, C22, C23, C24",0603,5,100nF,C14663
"C26, C27",0603,2,22uF,C84419
C7,0603,1,100pF,C14858
D1,LED_Dual_1.7_1.6,1,LED_DUAL_ACCA,C513363
L1,Inductor_SLW4018,1,2.2uH-DCR<0.1R-1.5A,C206341
L3,Inductor_SLW4018,1,1.5uH,C206395
"R1, R10",0603,2,100K-1%,C25803
"R11, R12",0603,2,10K,C25804
"R13, R14, R6",0603,3,1K,C21190
R15,0603,1,470kOhm,C23178
R16,0603,1,140kOhm,C321721
"R17, R2, R3, R7, R8",0603,5,200K-1%,C25811
R4,0603,1,24K-1%,C23352
R5,0805,1,0R03,C247605
R9,0603,1,3.6K-1%,C22980
U10,TSOT-23-6,1,~,C207630
U3,qfn48_6x6mm_Pitch0.4mm,1,AXP209,C2997895
U4,SOIC-14_3.9x8.7mm_P1.27mm,1,74LS73,C350539
U5,SOT-23-5,1,SY6280,C55136
U8,TSSOP-16_4.4x5mm_P0.65mm,1,SP3232ECY-L,C3028967
U9,SOIC-8_3.9x4.9mm_P1.27mm,1,PCF8563T,C7440
Y1,SMD3215-2P,1,32.768kHz,C32346
